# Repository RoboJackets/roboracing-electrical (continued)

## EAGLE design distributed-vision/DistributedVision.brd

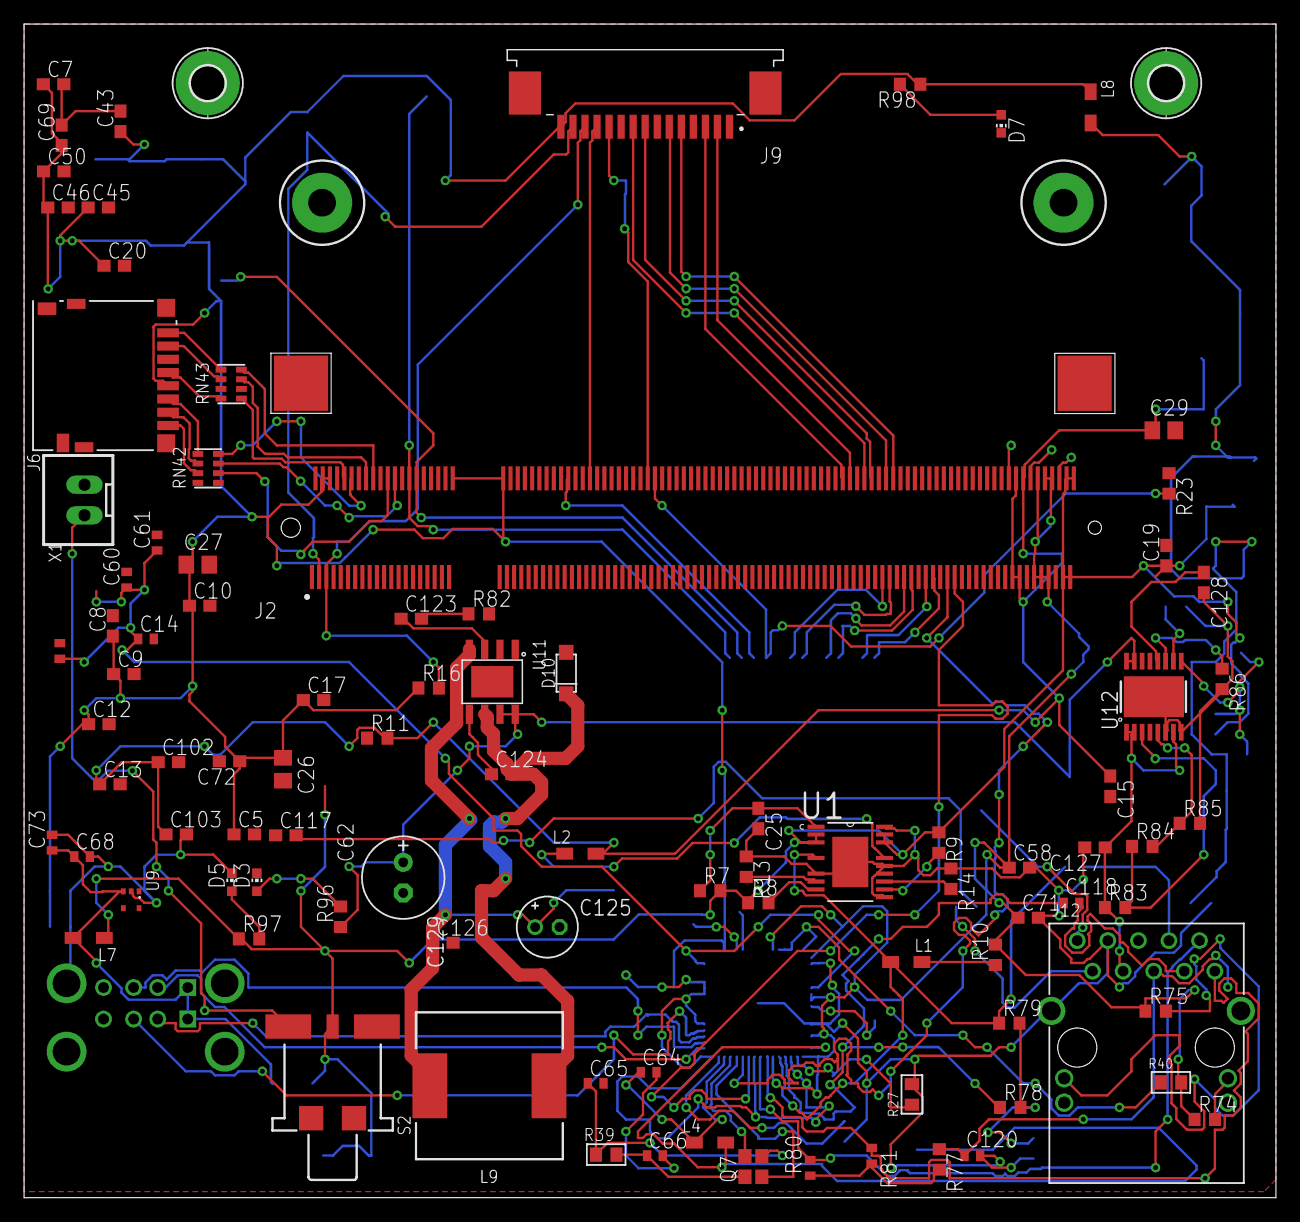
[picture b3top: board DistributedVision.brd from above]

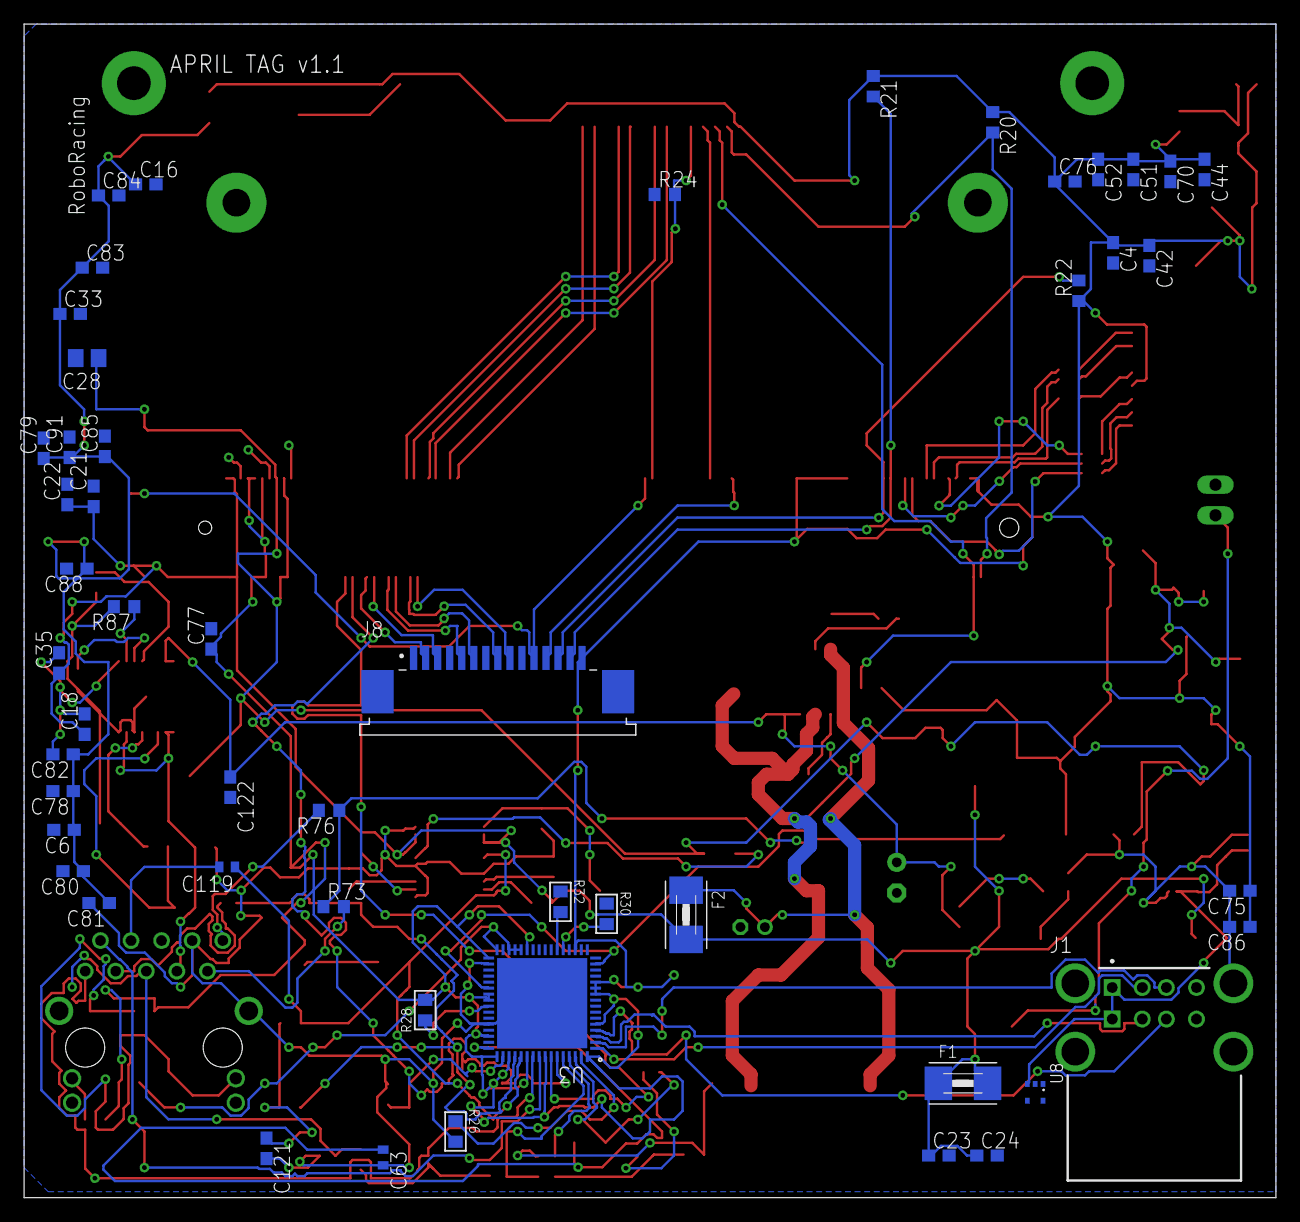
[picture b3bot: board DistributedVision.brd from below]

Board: 2 copper layers, 104.0 x 97.5 mm, 147 parts (51 on the bottom side), 95 nets.

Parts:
C4, C8, C9, C13, C18, C19, C20, C33, C51, C52, C58, C75, C76, C77, C80, C85, C86: 10nF; C0603
C5, C6, C10, C15, C16, C21, C42, C45, C46, C50, C69, C70, C71, C72, C78, C79, C81, C82, C83, C84, C88, C91: 100nF; C0603
C7, C12, C17, C22, C35, C102, C103: 10uF; C0603
C14, C64: 1uF; C0402
C23, C24: 22uF; C0603
C25: 470nF; C0603
C26, C27, C28, C29: 22uF; C0805
C43, C44: 4.7uF; C0603
C60, C63, C68: 100nF; C0402
C61: 10nF; C0402
C62: 4.7uF; C0402
C65, C66: 33pF; C0402
C73: 10uF; C0402
C117, C121: 10000pF; C0603
C118, C119: 10000pF; C0402
C120: 0.1uF; C0402
C122: 10000pF, 50V; C0603
C123: 0.022uF, 50V; C0603
C124, C126: 0.220uF; C0603
C125: 100uF; E2-5
C127: 1uF, 50V; C0603
C128: 2.2uF, 50V; C0603
C129: 100uF, 35V; E2,5-7
D3, D5, D7: GRN; CHIP-LED0603
D10: NTS260ESFT3G; SOD123FL_DIO
F1, F2: 2A; 1812
H1, H2: MOUNT-PAD-ROUND2.8; 2,8-PAD
J1: USBR-A-D-F-O-TH; SAMTEC_USBR-A-D-F-O-TH
J2: RASPBERRRY_COMPUTE_CM3; TE_1473149-4_WITH_CM3PLUS
J6: DM3D-SF; CONN8_DM3D-SF_HIR
J8, J9: 1-84952-5; TE_1-84952-5
J12: ARJM11C7-104-AB-EW2; CONN_EW_ABR
L1, L2: 4A; 0805
L4, L7, L8: 1.3A 120r; 0805
L9: 47uH; WE-PD_1210
Q7: 25 MHz; FA-20H
R7: 5.1k; R0603
R8, R9: 47k; R0603
R10: 31.6k; R0603
R11: 12.7k; R0603
R13, R14, R78, R79: 10k; R0603
R16, R20, R21, R22, R96: 4.7k; R0603
R23, R24: 100k; R0603
R26: 12k, 1.0%; RC0805N
R27: 12.4k, 1.0%; RC0805N
R28, R30, R32, R40: 4.7k; RC0805N
R39: 1M; RC0805N
R73, R76: 75, 1%; R0603
R74, R75, R98: 470; R0603
R77: 22, 1%; R0603
R80, R81: 49.9, 1%; R0402
R82: 22k; R0603
R83: 715k, 1%; R0603
R84: 20k, 1%; R0603
R85: 30.1k, 1%; R0603
R86: 11.8k, 1%; R0603
R87: 66.5k, 1%; R0603
R97: 330; R0603
RN42, RN43: 22; RA-4_1206
S2: 34EWMSP12M6RT
U1: LM26420XMH; SOP65P640X175-21N
U3: LAN9513-JZXQFN64_9X9MC_MCH-M; QFN64_9X9MC_MCH-M
U8, U9: SP3003-02; SC70-5
U11: IFX91041; SOIC-8-EXPOSED_PAD
U12: TPS26600PWPR; PWP0016H_N
X1: JST-XH-02-PIN-LONG-PAD; JST-XH-02-PACKAGE-LONG-PAD

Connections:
3V3_LED: D7.A, R98.2
5V_LED: D5.A, R97.2
5V_RAW: C124.2, D10.1, L9.1, U11.6
24V_LED: D3.A, R96.2
24_LOAD: R87.1, U12.10
+1.8V: C13.1, C15.1, C28.1, C29.1, C102.1, C103.1, J2.183, J2.184, J2.185, J2.186, L2.2, R11.2
+3.3V: C4.1, C5.1, C7.1, C8.1, C9.1, C10.1, C12.1, C17.1, C20.1, C26.1, C27.1, C42.1, C43.1, C44.1, C45.1, C46.1, C50.1, C51.1, C52.1, C58.1, C69.1, C70.1, C71.1, C72.1, C75.1, C76.1, C77.1, C86.1, J2.4, J2.6, J2.40, J2.42, J2.189, J2.190, J2.191, J2.192, J2.193, J2.194, J6.4, J8.15, J9.15, L8.1, R10.2, R16.1, R20.1, R21.1, R22.1, R28.2, R40.2, R74.1, R75.1, R98.1, U3.5, U3.10, U3.11, U3.12, U3.19, U3.27, U3.33, U3.39, U3.40, U3.46, U3.49, U3.51, U3.54, U3.57, U3.64
+3.3V-A: C6.1, C16.1, C33.1, C78.1, C79.1, C80.1, C81.1, C82.1, C83.1, C84.1, C85.1, C88.1, C91.1, L8.2
+3V3_A: R77.2, R80.1, R81.2
+5V: C18.1, C19.1, C21.1, C22.1, C23.1, C24.1, C35.1, F1.1, F1.2, F2.2, J2.197, J2.198, J2.199, J2.200, L7.1, R7.2, R8.1, R9.1, R97.1, S2.2, U1.2, U1.3, U1.18, U1.19
+5V_PREFUSE: C125.+, C126.1, F2.1, L9.2, U11.4
+24V: C127.1, J12.7, R83.1, U12.1, U12.2, U12.7
+24V_FUSE: C122.1, C129.+, R96.1, U11.7, U11.8, U12.15, U12.16
BVCC: S2.3, X1.1
CAM0_CN: J2.144, J9.8
CAM0_CP: J2.142, J9.9
CAM0_DN0: J2.138, J9.2
CAM0_DN1: J2.150, J9.5
CAM0_DP0: J2.136, J9.3
CAM0_DP1: J2.148, J9.6
CAM0_IO0: J2.82, J9.11, R24.2
CAM0_IO1: J2.66, J9.12
CAM0_SCL: J2.5, J9.13, R16.2
CAM0_SDA: J2.3, J9.14, R20.2
CAM1_CN: J2.149, J8.8
CAM1_CP: J2.147, J8.9
CAM1_DN0: J2.161, J8.2
CAM1_DN1: J2.155, J8.5
CAM1_DP0: J2.159, J8.3
CAM1_DP1: J2.153, J8.6
CAM1_IO0: J2.84, J8.11, R23.2
CAM1_IO1: J2.60, J8.12
CAM1_SCL: J2.30, J8.13, R22.2
CAM1_SDA: J2.28, J8.14, R21.2
CT: C120.1, J12.5, R77.1
FB1: L1.2, R10.1
GND: C4.2, C5.2, C6.2, C7.2, C8.2, C9.2, C10.2, C12.2, C13.2, C14.2, C15.2, C16.2, C17.2, C18.2, C19.2, C20.2, C21.2, C22.2, C23.2, C24.2, C25.2, C26.2, C27.2, C28.2, C29.2, C33.2, C35.2, C42.2, C43.2, C44.2, C45.2, C46.2, C50.2, C51.2, C52.2, C58.2, C60.2, C61.2, C62.2, C63.2, C64.2, C65.2, C66.2, C68.2, C69.2, C70.2, C71.2, C72.2, C73.2, C75.2, C76.2, C77.2, C78.2, C79.2, C80.2, C81.2, C82.2, C83.2, C84.2, C85.2, C86.2, C88.2, C91.2, C102.2, C103.2, C117.1, C120.2, C121.2, C122.2, C125.-, C126.2, C127.2, C129.-, D3.C, D5.C, D7.C, D10.2, J1.A04, J1.B04, J1.S1, J1.S2, J1.S3, J1.S4, J2.1, J2.7, J2.8, J2.13, J2.14, J2.19, J2.20, J2.25, J2.26, J2.31, J2.32, J2.37, J2.38, J2.43, J2.44, J2.49, J2.50, J2.55, J2.56, J2.61, J2.62, J2.67, J2.68, J2.73, J2.74, J2.79, J2.80, J2.85, J2.86, J2.91, J2.92, J2.97, J2.98, J2.103, J2.104, J2.109, J2.110, J2.115, J2.116, J2.121, J2.122, J2.127, J2.133, J2.134, J2.139, J2.140, J2.145, J2.146, J2.151, J2.152, J2.157, J2.163, J2.164, J2.168, J2.169, J2.170, J2.181, J2.182, J2.187, J2.188, J2.195, J2.196, J6.6, J8.1, J8.4, J8.7, J8.10, J9.1, J9.4, J9.7, J9.10, J12.8, J12.CH1, J12.CH2, R13.1, R14.1, R23.1, R24.1, R26.2, R27.2, R82.2, RN42.1, RN42.2, RN43.3, RN43.4, U1.7, U1.11, U1.14, U1.15, U1.20, U1.21, U3.34, U3.44, U3.65, U8.2, U9.2, U11.1, U11.2, U11.9, U12.9, X1.2
G_LED+: J12.L1, R75.2
unnamed: R13.2, U1.8
unnamed: C123.1, U11.3
unnamed: C25.1, R7.1, U1.1
unnamed: J12.9, R73.2
unnamed: J12.10, R76.2
unnamed: C124.1, U11.5
unnamed: C123.2, R82.1
unnamed: C117.2, R73.1, R76.1
unnamed: R83.2, R84.1, U12.3
unnamed: R84.2, R85.1, U12.5
unnamed: C128.1, U12.12
unnamed: R86.1, U12.11
unnamed: R8.2, U1.9
unnamed: J6.1, RN42.4
unnamed: J6.2, RN42.6
unnamed: J6.3, RN42.8
unnamed: J6.5, RN43.2
unnamed: J6.7, RN43.6
unnamed: J6.8, RN43.8
unnamed: C64.1, L4.1, U3.62
unnamed: C63.1, L4.2, U3.48
unnamed: R30.2, U3.21
unnamed: R32.2, U3.22
unnamed: R40.1, U3.28, U3.29, U3.30, U3.32
unnamed: Q7.3, U3.61
unnamed: Q7.1, U3.60
unnamed: C66.1, Q7.4, R39.2
unnamed: C65.1, Q7.2, R39.1
unnamed: R26.1, U3.63
unnamed: R28.1, U3.41
unnamed: R27.1, U3.50
RD_N: C119.2, J12.4
RD_P: C118.2, J12.3
RTN: C128.2, R85.2, R86.2, R87.2, U12.6, U12.8, U12.17
RX_FILTER: C121.1, R78.2, R79.2
RX_N: C119.1, L1.1, R79.1, U1.5, U3.53
RX_P: C118.1, R78.1, U3.52
RX_P1: R9.2, U1.12
SD_CLK: J2.10, RN43.1
SD_CMD: J2.12, RN42.7
SD_DAT0: J2.16, RN43.5
SD_DAT1: J2.18, RN43.7
SD_DAT2: J2.22, RN42.3
SD_DAT3: J2.24, RN42.5
TVCC: C68.1, C73.1, J1.A01, J1.B01, L7.2, U8.3, U9.3
TX_N: J12.2, R80.2, U3.56
TX_P: J12.1, R81.1, U3.55
USB0_N: J2.167, U3.58
USB0_P: J2.165, U3.59
USB2_N: J1.A02, U3.1
USB2_P: J1.A03, U3.2
USB3_N: J1.B02, U3.3
USB3_P: J1.B03, U3.4
USBDM4: L2.1, U1.16
USBDP4: R14.2, U1.13
VDD18CORE: C14.1, C60.1, C61.1, C62.1, U3.15, U3.38
Y_LED+: J12.L3, R74.2

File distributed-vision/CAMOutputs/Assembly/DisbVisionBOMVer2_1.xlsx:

Value | Designator | Footprint | Device | Quantity | DigiKey Part Number
0.022uF, 50V | C123 | C0603 | C-USC0603 | 1 | 1276-1104-1-ND
0.1uF | C120 | C0402 | C-USC0402 | 1 | 399-C0603X104K5RAC3316CT-ND
0.220uF | C124, C126 | C0603 | C-USC0603 | 2 | 478-1243-1-ND
1-84952-5 | J8, J9 | TE_1-84952-5 | 1-84952-5 | 2 | A101391CT-ND
1.3A 120r | L8 | 805 | INDUCTOR_0805 | 1 | 541-1406-1-ND
1.3A 120r | L4, L7 | 805 | INDUCTOR_0805 | 2 | 541-1406-1-ND
10000pF | C118, C119 | C0402 | C-USC0402 | 2 | 478-5007-1-ND
10000pF | C117, C121 | C0603 | C-USC0603 | 2 | 445-8116-1-ND
10000pF, 50V | C122 | C0603 | C-USC0603 | 1 | 478-1254-1-ND
100k | R23, R24 | R0603 | R-US_R0603 | 2 | 541-100KAYCT-ND
100nF | C72, C79 | C0603 | C-USC0603 | 2 | 445-5667-1-ND
100nF | C60, C63, C68 | C0402 | C-USC0402 | 3 | 1276-1001-1-ND
100nF | C5, C6, C10, C15, C16, C21, C42, C45, C46, C50, C69, C70, C71, C78, C81, C82, C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 | C0603 | C-USC0603 | 20 | 445-5667-1-ND
100uF | C125 | E2-5 | CPOL-USE2-5 | 1 | 445-6007-1-ND
100uF, 35V | C129 | E2,5-7 | CPOL-USE2.5-7 | 1 | 445-6007-1-ND
10k | R13, R14,R78,R79 | R0603 | R-US_R0603 | 4 | 1135-1057-1-ND
10nF | C61 | C0402 | C-USC0402 | 1 | 720-1362-1-ND
10nF | C4, C8, C9, C13, C18, C19, C20, C33, C51, C52, C58, C75, C76, C77, C80, C85, C86 | C0603 | C-USC0603 | 17 | 445-8116-1-ND
10uF | C73 | C0402 | C-USC0402 | 1 | 478-10059-1-ND
10uF | C7, C12, C17, C22, C35, C102, C103 | C0603 | C-USC0603 | 7 | 445-9065-1-ND
11.8k, 1% | R86 | R0603 | R-US_R0603 | 1 | 541-RCS060311K8FKEACT-ND
12.4k, 1.0% | R27 | RC0805N | ERJ-L06KF50MV | 1 | 541-12.4KTCT-ND
12.7k | R11 | R0603 | R-US_R0603 | 1 | 541-3584-1-ND
12k, 1.0% | R26 | RC0805N | ERJ-L06KF50MV | 1 | 541-10502-1-ND
1M | R39 | RC0805N | ERJ-L06KF50MV | 1 | 541-1.00MTCT-ND
1uF | C14, C64 | C0402 | C-USC0402 | 2 | 445-9066-1-ND
1uF, 50V | C127 | C0603 | C-USC0603 | 1 | 445-7468-1-ND
2.2uF, 50V | C128 | C0603 | C-USC0603 | 1 | 490-12332-1-ND
20k, 1% | R84 | R0603 | R-US_R0603 | 1 | 541-2993-1-ND
22 | RN42, RN43 | RA-4_1206 | RA-41206 | 2 | CAY16-22R0F4LFCT-ND
22k, 1% | R77 | R0603 | R-US_R0603 | 1 | 541-10441-1-ND
22k | R82 | R0603 | R-US_R0603 | 1 | 541-CRCW060322K0JNEACCT-ND
22uF | C23, C24 | C0603 | C-USC0603 | 2 | 1276-2868-1-ND
22uF | C26, C27, C28, C29 | C0805 | C-USC0805 | 4 | 445-11527-1-ND
25 MHz | Q7 | FA-20H | FA-20H | 1 | XC3051CT-ND
2A | F1, F2 | 1812 | PTCFUSE-1812 | 2 | SF-0603F200-2CT-ND
30.1k, 1% | R85 | R0603 | R-US_R0603 | 1 | 541-5345-1-ND
31.6k | R10 | R0603 | R-US_R0603 | 1 | 541-RCS060331K6FKEACT-ND
330 | R97 | R0603 | R-US_R0603 | 1 | 541-330GCT-ND
33pF | C65, C66 | C0402 | C-USC0402 | 2 | 445-1241-1-ND
34EWMSP12M6RT | S2 | 34EWMSP12M6RT | 34EWMSP12M6RT | 1 | GH7540CT-ND
4.7k | R28, R30, R32, R40 | RC0805N | ERJ-L06KF50MV | 4 | 541-CRCW08054K70JNEAIFCT-ND
4.7k | R16, R20, R21, R22, R96 | R0603 | R-US_R0603 | 5 | 541-4.7KGCT-ND
4.7uF | C62 | C0402 | C-USC0402 | 1 | 490-11980-1-ND
4.7uF | C43, C44 | C0603 | C-USC0603 | 2 | 1276-6794-1-ND
470 | R74, R75, R98 | R0603 | R-US_R0603 | 3 | 541-4055-1-ND
470nF | C25 | C0603 | C-USC0603 | 1 | 587-3476-1-ND
47k | R8, R9 | R0603 | R-US_R0603 | 2 | 541-4021-1-ND
47uH | L9 | WE-PD_1210 | 7447709470_7447709470 | 1 | 732-1246-1-ND
49.9, 1% | R80, R81 | R0402 | R-US_R0402 | 2 | 541-2963-1-ND
4A | L1, L2 | 805 | INDUCTOR_0805 | 2 | 541-1555-1-ND
5.1k | R7 | R0603 | R-US_R0603 | 1 | 541-2035-1-ND
66.5k, 1% | R87 | R0603 | R-US_R0603 | 1 | 541-CRCW060366K5FKEBCT-ND
715k, 1% | R83 | R0603 | R-US_R0603 | 1 | 311-715KHRCT-ND
75, 1% | R73, R76 | R0603 | R-US_R0603 | 2 | 541-2196-1-ND
ARJM11C7-104-AB-EW2 | J12 | CONN_EW_ABR | ARJM11C7-104-AB-EW2 | 1 | 535-14148-ND
DM3D-SF | J6 | CONN8_DM3D-SF_HIR | DM3D-SF | 1 | HR1941CT-ND
GRN | D3, D5, D7 | CHIP-LED0603 | LEDCHIP-LED0603 | 3 | 1497-1215-1-ND
IFX91041 | U11 | SOIC-8-EXPOSED_PAD | IFX91041 | 1 | IFX91041EJV50XUMA1CT-ND
JST-XH-02-PIN | X1 | JST-XH-02-PIN-LONG-PAD | JST-XH-02-PACKAGE-LONG-PAD | 1 | 455-2247-ND
LAN9513-JZXQF | U3 | QFN64_9X9MC_MCH-M | N64_9X9MC_MCH-M LAN9513-JZXQFN64_9X9MC_MCH-M | 1 | LAN9513-JZX-ND
LM26420XMH | U1 | SOP65P640X175-21N | LM26420XMH | 1 | 296-LM26420XMH/NOPB-ND
NTS260ESFT3G | D10 | SOD123FL_DIO | NTS260ESFT3G | 1 | NTS260ESFT3GOSCT-ND
RASPBERRRY_COMPUTE_CM3 | J2 | TE_1473149-4_WITH_CM3PLUS | RASPBERRRY_COMPUTE_CM3 | 1 | 1690-1031-ND
SP3003-02 | U8, U9 | SC70-5 | SP3003-02 | 2 | F3302CT-ND
TPS26600PWPR | U12 | PWP0016H_N | TPS26600PWPR | 1 | 296-47292-1-ND
USBR-A-D-F-O-TH | J1 | SAMTEC_USBR-A-D-F-O-TH | USBR-A-D-F-O-TH | 1 | SAM10376-ND

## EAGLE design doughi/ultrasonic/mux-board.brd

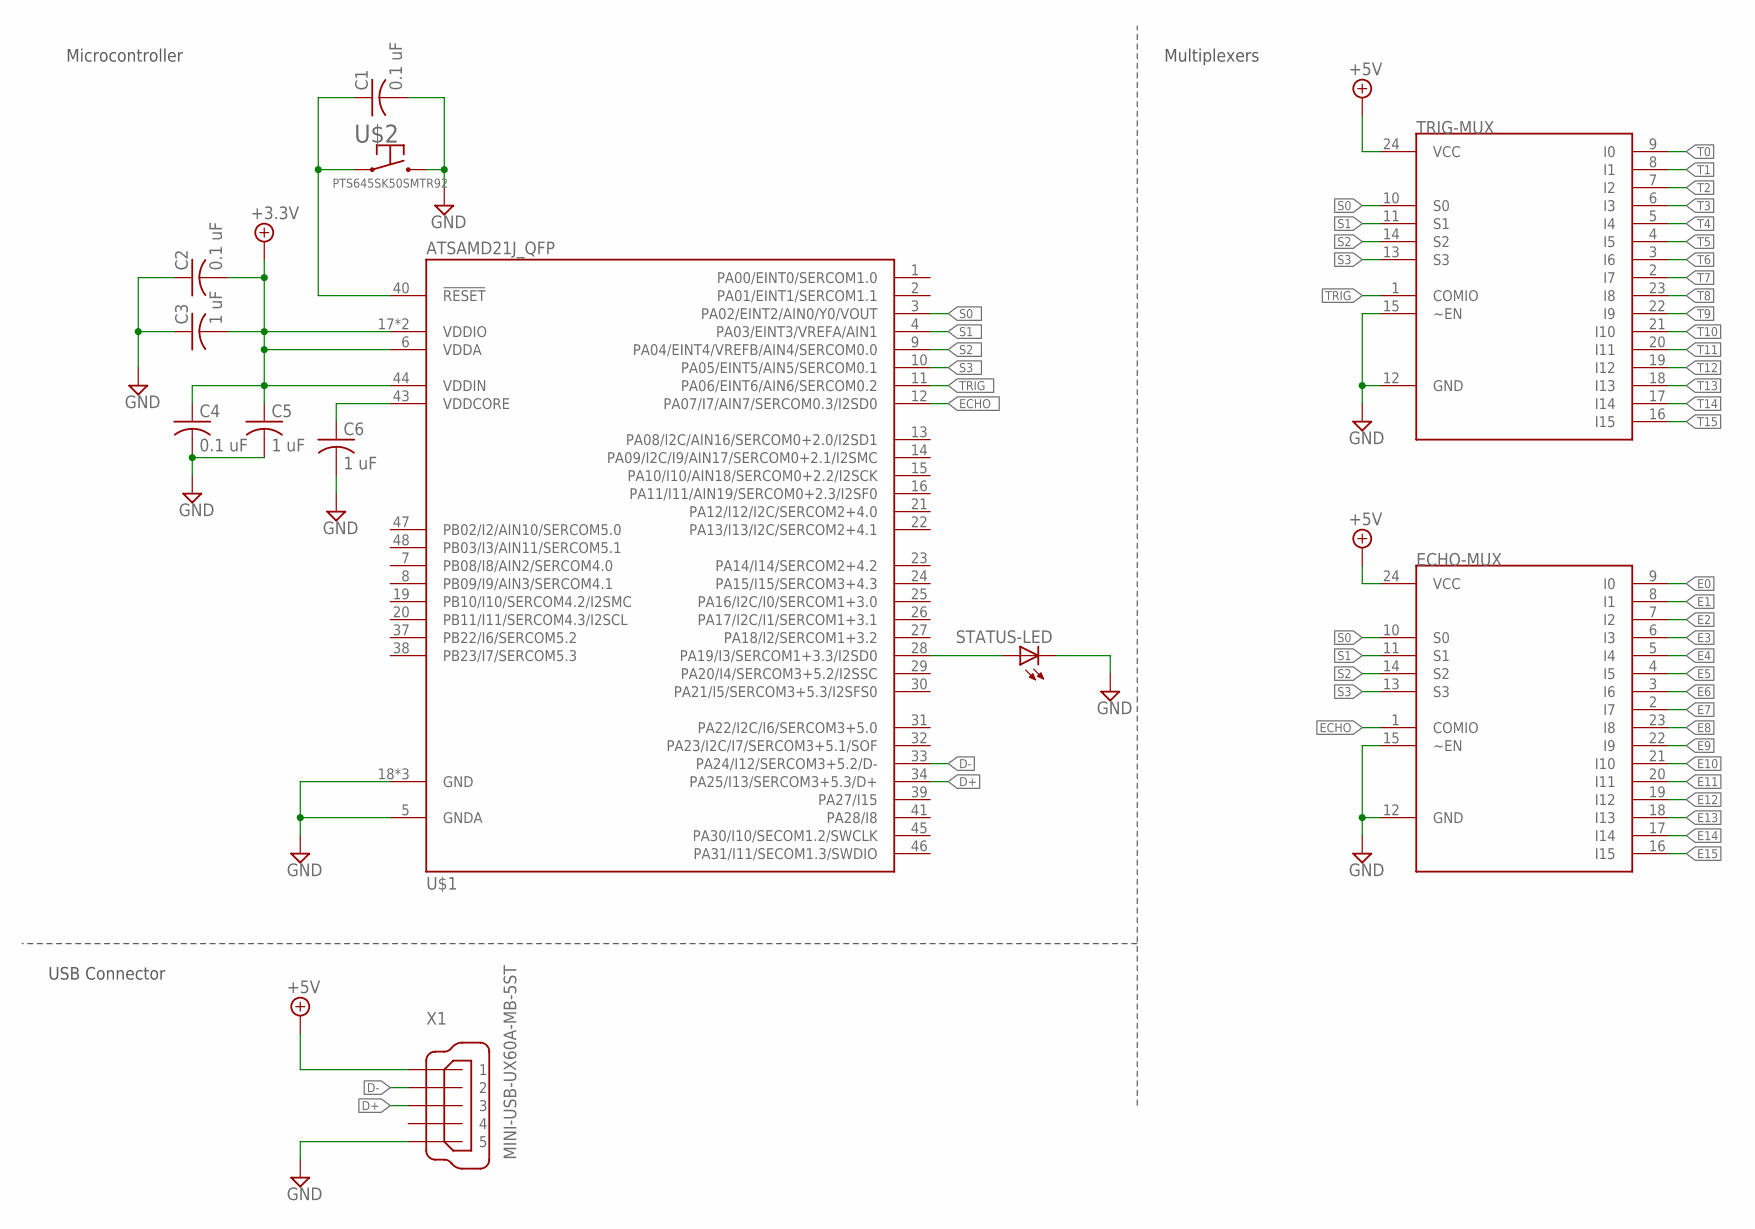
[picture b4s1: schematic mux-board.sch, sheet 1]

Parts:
C1, C2, C4: 0.1 uF; C0603
C3, C5, C6: 1 uF; C0603
ECHO-MUX: CD74HC4067; SO24R
STATUS-LED: LEDSML0603; SML0603
TRIG-MUX: CD74HC4067; SO24R
U$1: ATSAMD21J_QFP; TQFP48_7MM
U$2: PTS645SK50SMTR92
X1: MINI-USB-UX60A-MB-5ST; UX60A-MB-5ST

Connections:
+3.3V: C2.2, C3.2, C4.1, C5.1, U$1.6 (VDDA), U$1.17 (VDDIO), U$1.36 (VDDIO), U$1.44 (VDDIN); also elsewhere on the board
D+: U$1.34 (PA25/I13/SERCOM3+5.3/D+), X1.3
D-: U$1.33 (PA24/I12/SERCOM3+5.2/D-), X1.2
E0: ECHO-MUX.9 (I0); also elsewhere on the board
E1: ECHO-MUX.8 (I1); also elsewhere on the board
E2: ECHO-MUX.7 (I2); also elsewhere on the board
E3: ECHO-MUX.6 (I3); also elsewhere on the board
E4: ECHO-MUX.5 (I4); also elsewhere on the board
E5: ECHO-MUX.4 (I5); also elsewhere on the board
E6: ECHO-MUX.3 (I6); also elsewhere on the board
E7: ECHO-MUX.2 (I7); also elsewhere on the board
E8: ECHO-MUX.23 (I8); also elsewhere on the board
E9: ECHO-MUX.22 (I9); also elsewhere on the board
E10: ECHO-MUX.21 (I10); also elsewhere on the board
E11: ECHO-MUX.20 (I11); also elsewhere on the board
E12: ECHO-MUX.19 (I12); also elsewhere on the board
E13: ECHO-MUX.18 (I13); also elsewhere on the board
E14: ECHO-MUX.17 (I14); also elsewhere on the board
E15: ECHO-MUX.16 (I15); also elsewhere on the board
ECHO: ECHO-MUX.1 (COMIO); also elsewhere on the board
ECHO_: U$1.12 (PA07/I7/AIN7/SERCOM0.3/I2SD0); also elsewhere on the board
GND: C1.2, C2.1, C3.1, C4.2, C5.2, C6.2, ECHO-MUX.12 (GND), ECHO-MUX.15 (~EN), STATUS-LED.C, TRIG-MUX.12 (GND), TRIG-MUX.15 (~EN), U$1.5 (GNDA), U$1.18 (GND), U$1.35 (GND), U$1.42 (GND), U$2.3 (2), U$2.4 (2), X1.5; also elsewhere on the board
unnamed: C6.1, U$1.43 (VDDCORE)
unnamed: C1.1, U$1.40 (!RESET), U$2.1, U$2.2 (1)
unnamed 24: STATUS-LED.A, U$1.28 (PA19/I3/SERCOM1+3.3/I2SD0); also elsewhere on the board
unnamed 25: U$1.27 (PA18/I2/SERCOM1+3.2); also elsewhere on the board
S0: ECHO-MUX.10 (S0), TRIG-MUX.10 (S0); also elsewhere on the board
S0_: U$1.3 (PA02/EINT2/AIN0/Y0/VOUT); also elsewhere on the board
S1: ECHO-MUX.11 (S1), TRIG-MUX.11 (S1); also elsewhere on the board
S1_: U$1.4 (PA03/EINT3/VREFA/AIN1); also elsewhere on the board
S2: ECHO-MUX.14 (S2), TRIG-MUX.14 (S2); also elsewhere on the board
S2_: U$1.9 (PA04/EINT4/VREFB/AIN4/SERCOM0.0); also elsewhere on the board
S3: ECHO-MUX.13 (S3), TRIG-MUX.13 (S3); also elsewhere on the board
S3_: U$1.10 (PA05/EINT5/AIN5/SERCOM0.1); also elsewhere on the board
T0: TRIG-MUX.9 (I0); also elsewhere on the board
T1: TRIG-MUX.8 (I1); also elsewhere on the board
T2: TRIG-MUX.7 (I2); also elsewhere on the board
T3: TRIG-MUX.6 (I3); also elsewhere on the board
T4: TRIG-MUX.5 (I4); also elsewhere on the board
T5: TRIG-MUX.4 (I5); also elsewhere on the board
T6: TRIG-MUX.3 (I6); also elsewhere on the board
T7: TRIG-MUX.2 (I7); also elsewhere on the board
T8: TRIG-MUX.23 (I8); also elsewhere on the board
T9: TRIG-MUX.22 (I9); also elsewhere on the board
T10: TRIG-MUX.21 (I10); also elsewhere on the board
T11: TRIG-MUX.20 (I11); also elsewhere on the board
T12: TRIG-MUX.19 (I12); also elsewhere on the board
T13: TRIG-MUX.18 (I13); also elsewhere on the board
T14: TRIG-MUX.17 (I14); also elsewhere on the board
T15: TRIG-MUX.16 (I15); also elsewhere on the board
TRIG: TRIG-MUX.1 (COMIO); also elsewhere on the board
TRIG_: U$1.11 (PA06/EINT6/AIN6/SERCOM0.2); also elsewhere on the board
X3-1: U$1.1 (PA00/EINT0/SERCOM1.0); also elsewhere on the board
X3-2: U$1.2 (PA01/EINT1/SERCOM1.1); also elsewhere on the board

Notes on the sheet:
Microcontroller
Multiplexers
USB Connector

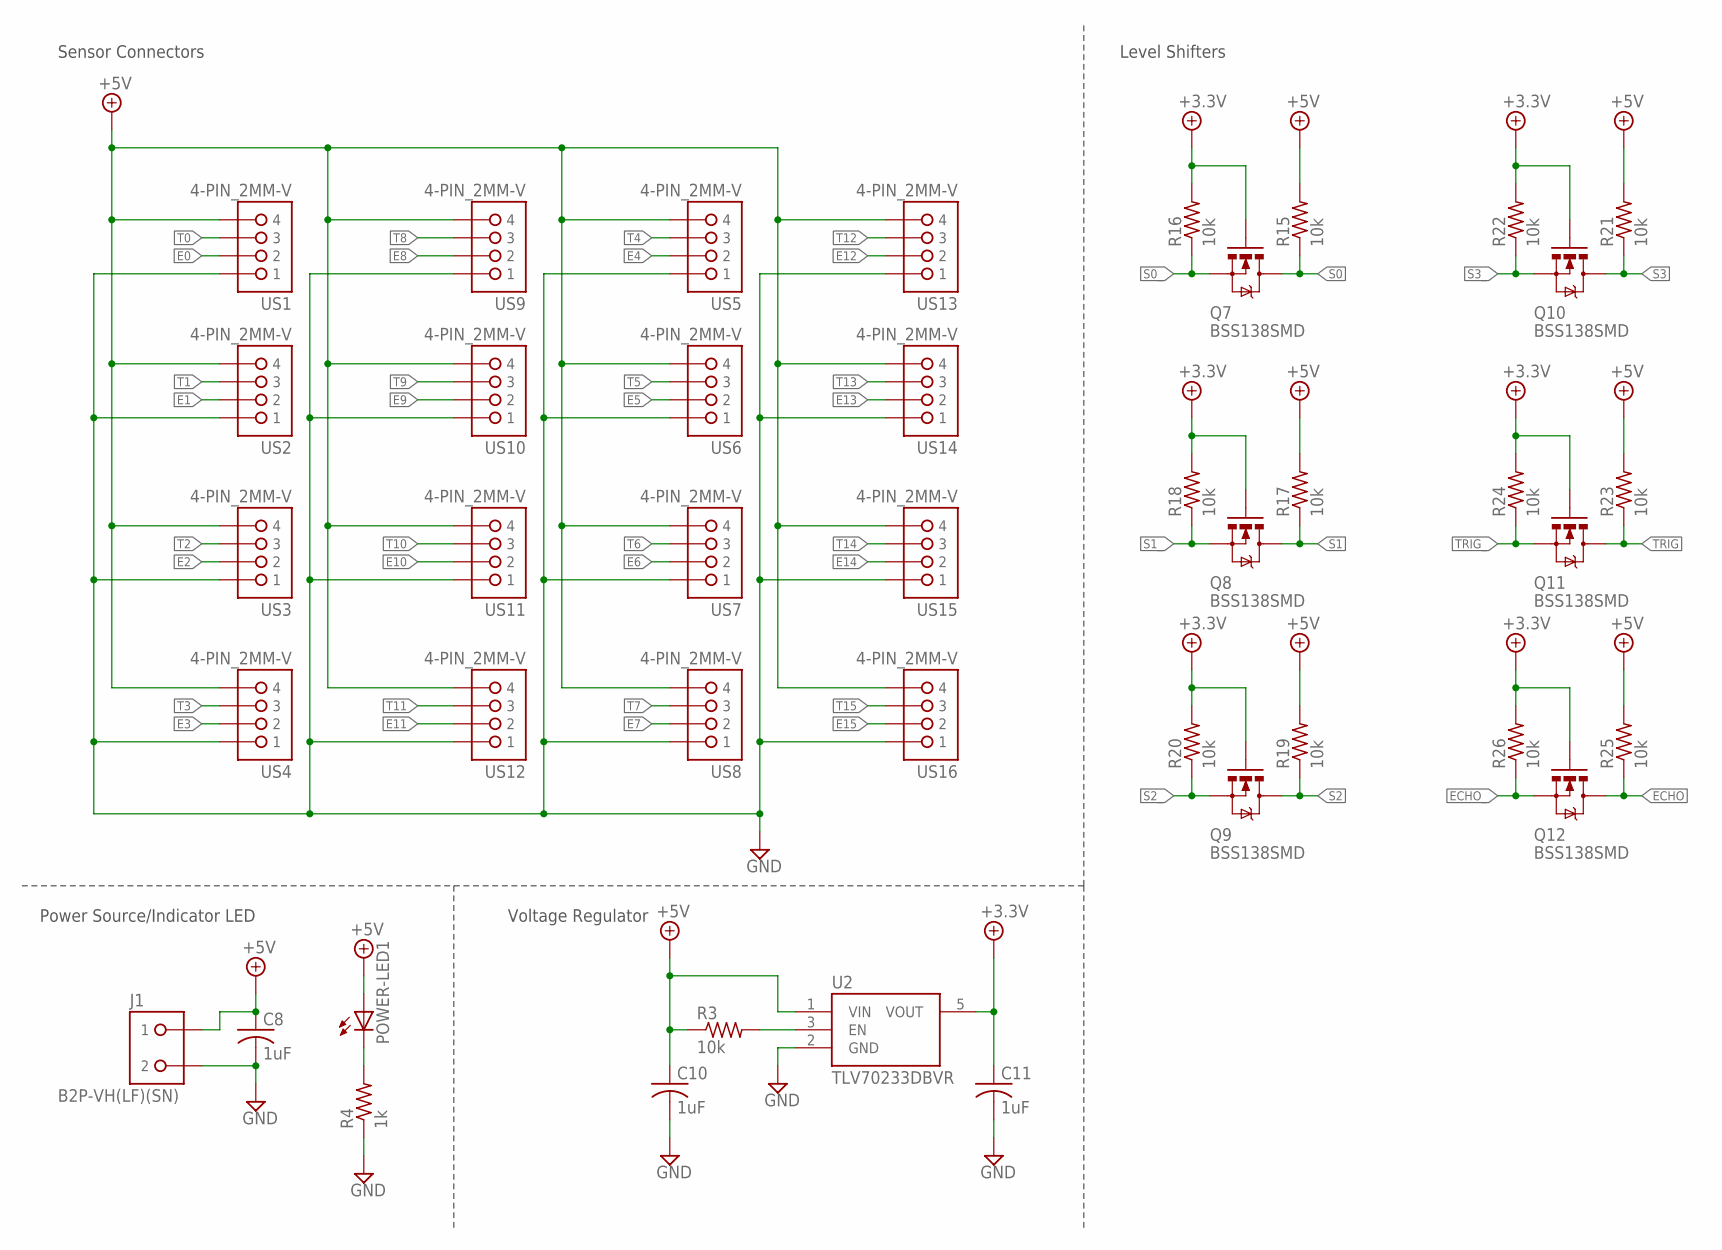
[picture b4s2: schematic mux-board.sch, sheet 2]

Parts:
C8, C10, C11: 1uF; C0603
J1: B2P-VH(LF)(SN); B2P
POWER-LED1: LEDSML0603; SML0603
Q7, Q8, Q9, Q10, Q11, Q12: BSS138SMD; SPARKFUN_SOT23-3
R3, R15, R16, R17, R18, R19, R20, R21, R22, R23, R24, R25, R26: 10k; R0603
R4: 1k; R0603
U2: TLV70233DBVR; SOT-23-5
US1, US2, US3, US4, US5, US6, US7, US8, US9, US10, US11, US12, US13, US14, US15, US16: 4-PIN_2MM-V; 2MM-4-V

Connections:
+3.3V: C11.1, Q7.1 (G), Q8.1 (G), Q9.1 (G), Q10.1 (G), Q11.1 (G), Q12.1 (G), R16.2, R18.2, R20.2, R22.2, R24.2, R26.2, U2.5 (VOUT); also elsewhere on the board
E0: US1.2; also elsewhere on the board
E1: US2.2; also elsewhere on the board
E2: US3.2; also elsewhere on the board
E3: US4.2; also elsewhere on the board
E4: US5.2; also elsewhere on the board
E5: US6.2; also elsewhere on the board
E6: US7.2; also elsewhere on the board
E7: US8.2; also elsewhere on the board
E8: US9.2; also elsewhere on the board
E9: US10.2; also elsewhere on the board
E10: US11.2; also elsewhere on the board
E11: US12.2; also elsewhere on the board
E12: US13.2; also elsewhere on the board
E13: US14.2; also elsewhere on the board
E14: US15.2; also elsewhere on the board
E15: US16.2; also elsewhere on the board
ECHO: Q12.3 (D), R25.1; also elsewhere on the board
ECHO_: Q12.2 (S), R26.1; also elsewhere on the board
GND: C8.2, C10.2, C11.2, J1.2, R4.1, U2.2 (GND), US1.1, US2.1, US3.1, US4.1, US5.1, US6.1, US7.1, US8.1, US9.1, US10.1, US11.1, US12.1, US13.1, US14.1, US15.1, US16.1; also elsewhere on the board
unnamed: R3.2, U2.3 (EN)
unnamed: POWER-LED1.C, R4.2
S0: Q7.3 (D), R15.1; also elsewhere on the board
S0_: Q7.2 (S), R16.1; also elsewhere on the board
S1: Q8.3 (D), R17.1; also elsewhere on the board
S1_: Q8.2 (S), R18.1; also elsewhere on the board
S2: Q9.3 (D), R19.1; also elsewhere on the board
S2_: Q9.2 (S), R20.1; also elsewhere on the board
S3: Q10.3 (D), R21.1; also elsewhere on the board
S3_: Q10.2 (S), R22.1; also elsewhere on the board
T0: US1.3; also elsewhere on the board
T1: US2.3; also elsewhere on the board
T2: US3.3; also elsewhere on the board
T3: US4.3; also elsewhere on the board
T4: US5.3; also elsewhere on the board
T5: US6.3; also elsewhere on the board
T6: US7.3; also elsewhere on the board
T7: US8.3; also elsewhere on the board
T8: US9.3; also elsewhere on the board
T9: US10.3; also elsewhere on the board
T10: US11.3; also elsewhere on the board
T11: US12.3; also elsewhere on the board
T12: US13.3; also elsewhere on the board
T13: US14.3; also elsewhere on the board
T14: US15.3; also elsewhere on the board
T15: US16.3; also elsewhere on the board
TRIG: Q11.3 (D), R23.1; also elsewhere on the board
TRIG_: Q11.2 (S), R24.1; also elsewhere on the board

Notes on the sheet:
Voltage Regulator
Level Shifters
Sensor Connectors
Power Source/Indicator LED

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
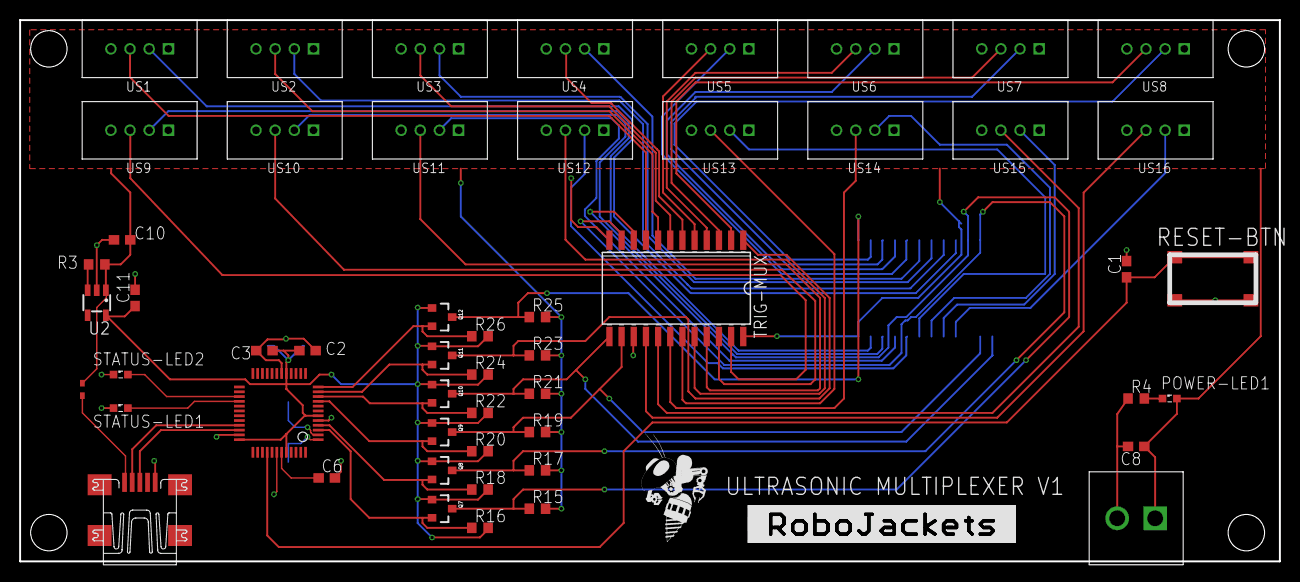
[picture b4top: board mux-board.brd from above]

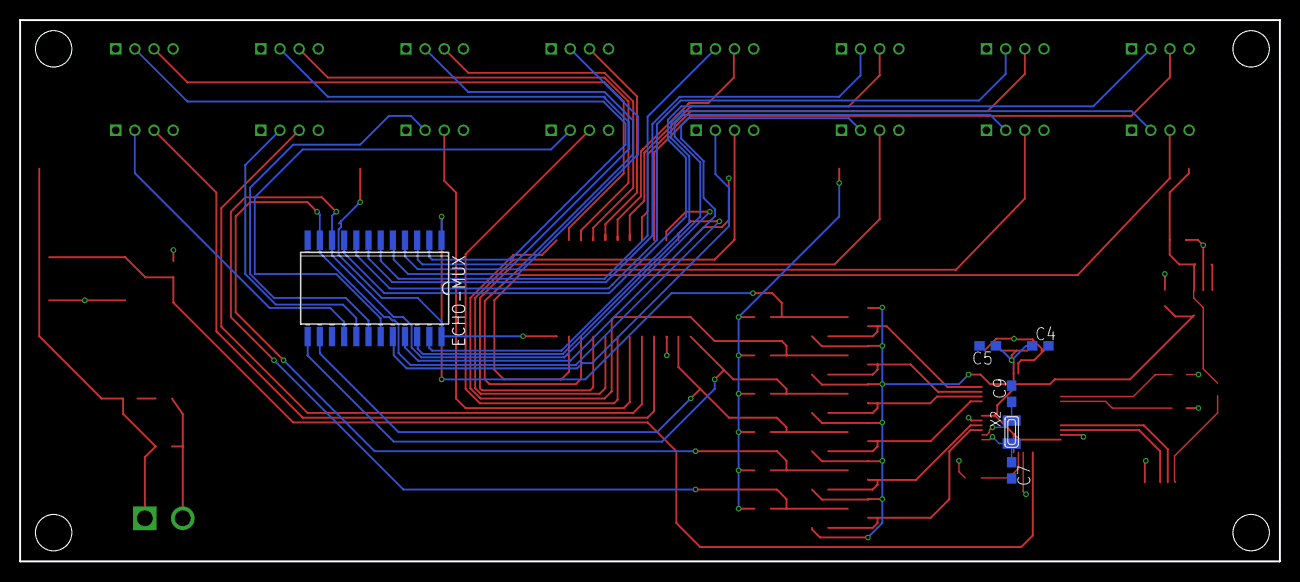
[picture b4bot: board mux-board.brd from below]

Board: 2 copper layers, 131.5 x 56.5 mm, 61 parts (6 on the bottom side), 58 nets.

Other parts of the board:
C7, C9: 22pF; C0603
STATUS-LED1, STATUS-LED2: SML0603
U$3: ROBOBUZZ_0.6X
U$4: ROBOJACKETS
U$5: RB521S30T1G; SOD523
X2: 32.768; XTAL3215

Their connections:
GND: C7.2, C9.2, STATUS-LED1.C, STATUS-LED2.C; also elsewhere on the board
unnamed 24: STATUS-LED1.A; also elsewhere on the board
unnamed 25: STATUS-LED2.A; also elsewhere on the board
X3-1: C7.1, X2.P$1; also elsewhere on the board
X3-2: C9.1, X2.P$2; also elsewhere on the board
